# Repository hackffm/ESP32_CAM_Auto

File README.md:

# ESP32_CAM_Auto
ESP32 Camera FPV Car - some description also on our [Hackerspace-FFM e.V. FPV-Roboter page](https://www.hackerspace-ffm.de/wiki/index.php?title=FPV-Roboter)

# Software setup
## Initial programming of ESP32 CAM Module
Connect it to USB-Serial-Board, hit `Pioarduino -> Project Tasks -> esp32cam -> Custom -> Initial Erase + Flash + FS + Monitor`. 

## Architecture infos
- LittleFS is used to store and retrieve WiFi credentials, botname and motor configs. This usually survives a FW update if LittleFS is not uploaded as well. Defaults are used, but LittleFS must be initialized. 
- Camera streams over http port 81 in MJPG mode - this guarantees lowest latency as next frame is only tranferred if current frame was delivered. Usually no significant buffering is used in browsers (this is different for eg RTSP that is why it is not used)
- Code is optimized for OV3660 cameras and support OV2640 cameras. ESP32 CAM boards have known issues with extreme WiFi lag due EMI issues with camera clock signal. We are using the following trick: Reduce external camera clock from 20Mhz to 8Mhz, but then using camera interanl PLL to get same speed again, that way we face much less interference issues.
- http deliveres index.htm and info and action point on port 80. Info streams every second info to browser like fps, but also names for sliders. action is used for controlling everything that is send from browser to the ESP (steering but also settings).
- pwmThing class encapsulates all PWM actions to control LED brightness, set motor speed and servo positions.
- Care must be taken that PWM stuff like analogWrite usually used high-speed timers, but camera clock is using low-speed timers. Arduino does not know about the already used camera timers, but as it uses high-speed timers instead there is no conflict.

# Hardware setup
## Cabling with special PCB
With the special PCB cabling is as easy as connecting left and right motor to the upper 2pin row of the headers and the servo to the lower 3pin row of the headers. For servo, the control line (typical the yellow cable) goes to where the pin is missing on the row above.
If servo does not work, you might need to turn the connector - as long as all 3 pins are connected nothing should broke even if the connector is in the wrong direction. For motor, check that the motors turn forward if you control the joystick forward, otherwise just turn the 2pin connector to change the motor direction of that motor that rotates in the wrong direction.

Supply power from Power Bank via USB-C cable to PCB to turn on the robot. Beware that the PCB does not include the programming hardware for the ESP-CAM - you have to program the ESP-CAM module with a separate programming adapter and then transfer it to the motor driver PCB.

PCB preparation: The idea is that you cut Pin 1 (the one with the square pad on the PCB) away to get a 3+2 pol connector from that originally 2x3 pol connector.
## Manual cabling
- For full-bridge motor drivers connect inputs to 12+13 and 15+14, add connectors to the motors that you can easily swap or turn the motor lines to adjust for correct drive direction
- For 360° servos just pick two of the available pins and set them up via web interface for left and right motor
- We used an USB A plug and a power supply for suppy. In such a case wire separate cables for motors and for ESP32 beginning from USB plug to avoid issues that motor starting currents are affecting ESP32

See the following picture how we did it:

## Usable pins
Pins can be redefined via Webinterface but on ESP32 CAM only the following pins are selectable and usable: 
- -1 (if pin or function not needed)
- 2, 12, 13, 14, 15 (free for use, SD card can not be used as these are also for SD card)
- 3 (if used, serial RX is not available anymore)

The following pins can not be used even if they are available on the ESP32 CAM board:
- 0 is used for camera clock signal
- 16 is internally used for PSRAM
- 1 is used for serial TX
- 4 is controlling the white flash LED
- 33 is controlling the red internal LED (might be usable if RedLed PWMThing is connected to pin -1)

## Supported motors
Both servos and full-bridge motor drivers are supported. Currently only seperate left- and right-motor are supported (no steering servo). Servos can then be 360deg servos used as motors, adjust min/zero/max limits for servos, zero is where 360deg servos does not turn (but they are stopped if appropriate servo variant is selected anyway).

# Usage
## LED indications
Slow breathing red LED means normal operation and having a valid WiFi connection. You should be able to control your robot via website of the IP or the name the robot (default: http://cambot.local)

Fast breathing red LED means robot has not found a valid WiFi connection and is acting as WiFi access point. Scan you WiFi environment, connect to the WiFi that matches your robot name (default: cambot), and then go to http://192.168.4.1 to either control your robot directly or connect it to your home WiFi using the Settings area, where you could also scan for your WiFi access points. Beware that the ESP-CAM is 2.4GHz only, so you can connect it only access points that support 2.4GHz WiFi.

No breathing or blinking or off: Something is broken or not powered. If white LED blinks two times the modul could not start the camera module - so check the connection to the camera module first. Beware that to open the camera connector you have to twist the black element by 90° (meaning pulling it away from PCB surface) and not pull it along the PCB. Currently supported camera modules: OV2640 or OV3660 (recommended).

# Known issues
## It does not compile
Uninstall ESP32 core modules in Platform-IO first to force installing newest ones.

### This versions gave a running config
PACKAGES: 
 - contrib-piohome @ 3.4.4 
 - framework-arduinoespressif32 @ 3.3.7 
 - framework-arduinoespressif32-libs @ 5.5.0+sha.87912cd291 
 - tool-esp-rom-elfs @ 2024.10.11 
 - tool-esptoolpy @ 5.1.2 
 - toolchain-xtensa-esp-elf @ 14.2.0+20251107

## Connection issues
- Check Serial output for IP address and if Wifi connection worked.
- Most browsers need at least a slash at the end to not trigger the search engine, try `cambot/`first.
- Name server often have issues, mDNS is also active, try `cambot.local/`if IP can not be resolved.
- Some browsers tries always https, but only http is supported now, try `http://cambot.local`in such case.
- Last resort enter ip address in browser
- If WiFi credentials are not set, either set them via Serial terminal or connect to access point of the device, then open `http://192.168.4.1/`and set there Wifi SSID + password, then power cycle.

## FPS 
Ok, you want the picture as smooth as possible, why limit FPS then? If WiFi is too much congested, everything starts getting sluggy, especially if more than one FPV car is operated it can make sense to limit the frame rate to leave some room for other players. WiFi at 2.4 GHz can transmit around 3,000 kBytes/s (but an ESP32 max out usually already at 1,000 kBytes/s due internal limits), depending on quality settings and picture size we integrated at least 4 fpv cars in the band without issues simultaneously. Keep an eye on RSSI, if it falls below -70 dBm the WiFi bandwith starts to be limited significantly affecting also the frame rate of that vehicle.  

## Camera overheating
Especially the OV3660 moduls are working on ESP32 CAM boards, but are operated out of voltage specifications there. Therefore they are more prone to heat up - glue them with thin double sided tape to the SD card holder to give them a little more cooling surface. Camera is specified to operate with best picture quality up to 50°C, they are specified to allow operation up to 70°C, we see it often a little bit higher than that but it seems to be ok. As said, issue is that OV2640 is usually prefered over OV3660 du to better picture and speed but are more prone to overheating.

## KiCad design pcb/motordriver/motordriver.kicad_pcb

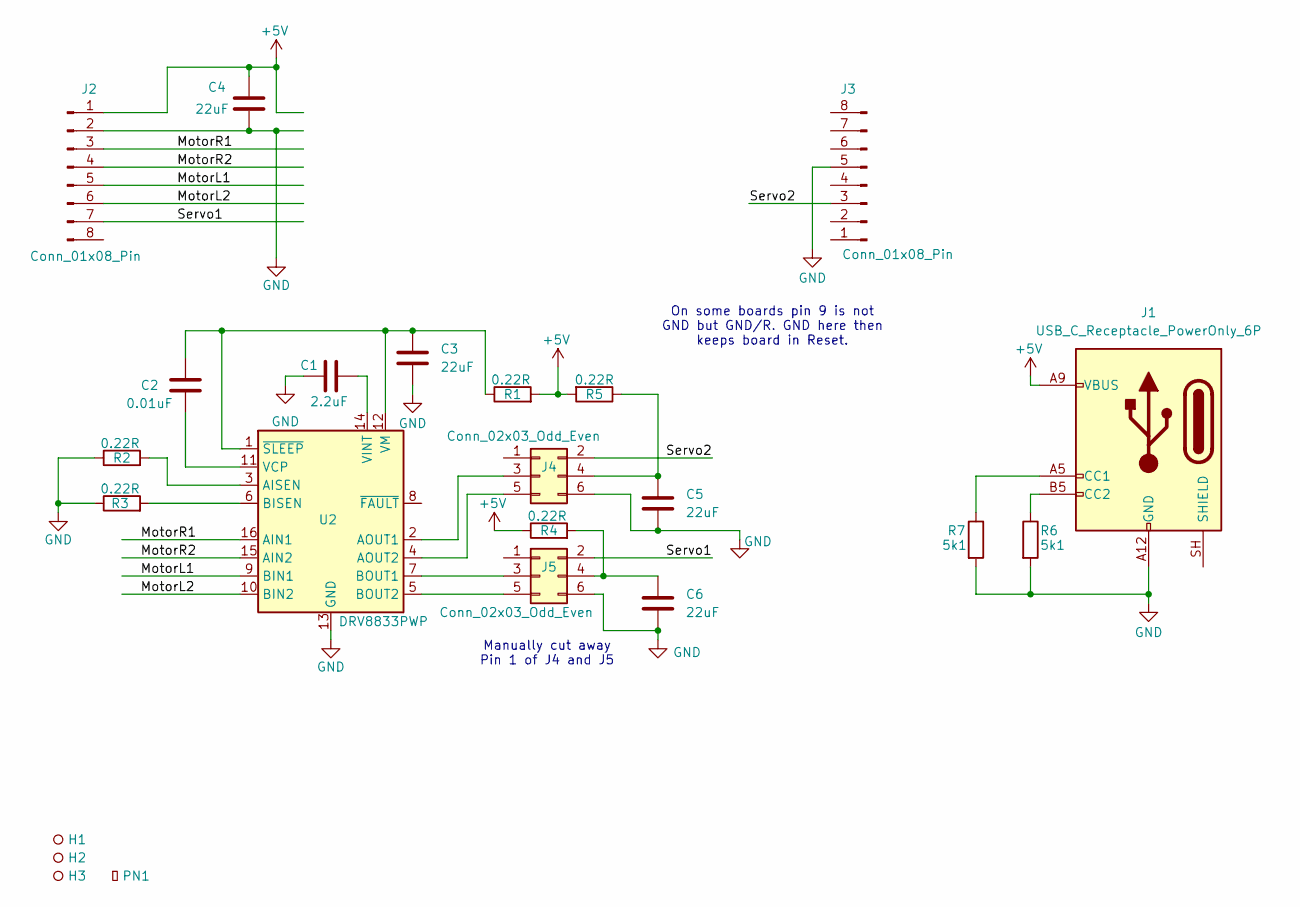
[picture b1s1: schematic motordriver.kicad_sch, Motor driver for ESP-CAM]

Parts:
C1: 2.2uF; C_0805_2012Metric; LCSC C377773
C2: 0.01uF; C_0603_1608Metric; LCSC C57112
C3, C4, C5, C6: 22uF; C_1206_3216Metric; LCSC C12891
H1, H2, H3: Hole_Tooling_JLCPCB
J1: USB_C_Receptacle_PowerOnly_6P; USB_C_Receptacle_HRO_TYPE-C-31-M-17; LCSC C283540
J2, J3: Conn_01x08_Pin; PinSocket_1x08_P2.54mm_Vertical; LCSC C22438158
J4, J5: Conn_02x03_Odd_Even; PinHeader_2x03_P2.54mm_Horizontal; LCSC C492431
PN1: Part_Num_JLCPCB
R1, R2, R3, R4, R5: 0.22R; R_1206_3216Metric; LCSC C327006
R6, R7: 5k1; R_0603_1608Metric; LCSC C23186
U2: DRV8833PWP; HTSSOP-16-1EP_4.4x5mm_P0.65mm_EP3.4x5mm_Mask2.46x2.31mm_The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; LCSC C50506

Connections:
+5V: C4.2, J1.A9 (VBUS), J1.B9 (VBUS), J2.1, R1.2, R4.1, R5.2
/MotorL1: J2.5, U2.9 (BIN1)
/MotorL2: J2.6, U2.10 (BIN2)
/MotorR1: J2.3, U2.16 (AIN1)
/MotorR2: J2.4, U2.15 (AIN2)
/Servo1: J2.7, J5.2
/Servo2: J3.3, J4.2
GND: C1.1, C3.2, C4.1, C5.2, C6.2, J1.A12 (GND), J1.B12 (GND), J2.2, J3.5, J4.6, J5.6, R2.1, R3.1, R6.2, R7.2, U2.13 (GND), U2.17 (GND)
unnamed: J1.A5 (CC1), R7.1
unnamed: J1.B5 (CC2), R6.1
unnamed: J4.3, U2.2 (AOUT1)
unnamed: C5.1, J4.4, R5.1
unnamed: J4.5, U2.4 (AOUT2)
unnamed: J5.3, U2.7 (BOUT1)
unnamed: C6.1, J5.4, R4.2
unnamed: J5.5, U2.5 (BOUT2)
unnamed: R2.2, U2.3 (AISEN)
unnamed: R3.2, U2.6 (BISEN)
unnamed: C2.2, U2.11 (VCP)
unnamed: C1.2, U2.14 (VINT)
unnamed: C2.1, C3.1, R1.1, U2.1 (~SLEEP), U2.12 (VM)

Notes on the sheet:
Manually cut away Pin 1 of J4 and J5
On some boards pin 9 is not GND but GND/R. GND here then keeps board in Reset.

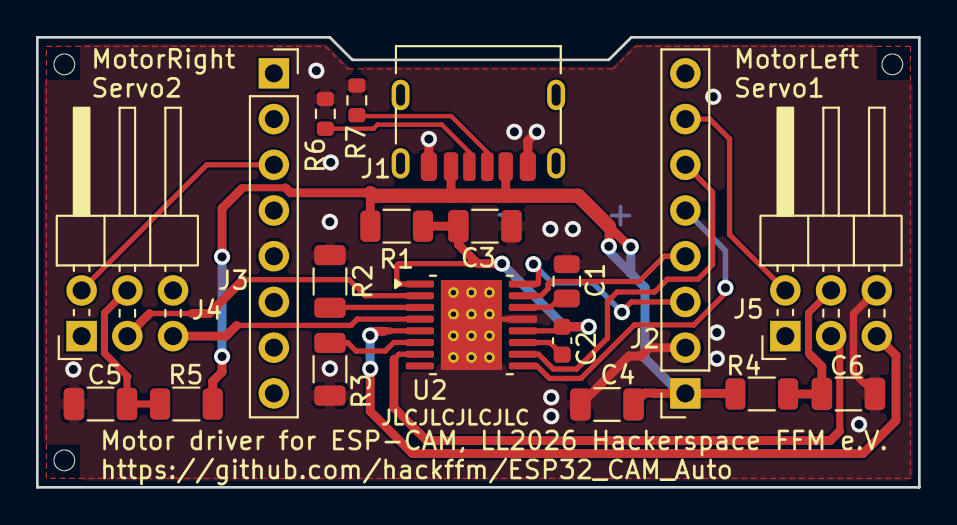
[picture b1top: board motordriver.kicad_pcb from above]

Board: 2 copper layers, 49.0 x 25.0 mm, 23 parts (0 on the bottom side), 21 nets.

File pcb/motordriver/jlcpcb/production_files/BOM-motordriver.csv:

Comment,Designator,Footprint,LCSC,Quantity
0.01uF,C2,C_0603_1608Metric,C57112,1
0.22R,"R1,R2,R3,R4,R5",R_1206_3216Metric,C327006,5
2.2uF,C1,C_0805_2012Metric,C377773,1
22uF,"C3,C4,C5,C6",C_1206_3216Metric,C12891,4
5k1,"R6,R7",R_0603_1608Metric,C23186,2
Conn_01x08_Pin,"J2,J3",PinSocket_1x08_P2.54mm_Vertical,C22438158,2
Conn_02x03_Odd_Even,"J4,J5",PinHeader_2x03_P2.54mm_Horizontal,C492431,2
DRV8833PWP,U2,HTSSOP-16-1EP_4.4x5mm_P0.65mm_EP3.4x5mm_Mask2.46x2.31mm_ThermalVias,C50506,1
USB_C_Receptacle_PowerOnly_6P,J1,USB_C_Receptacle_HRO_TYPE-C-31-M-17,C283540,1
~,H3,Hole_Tooling_JLCPCB,,1
~,H2,Hole_Tooling_JLCPCB,,1
~,H1,Hole_Tooling_JLCPCB,,1
~,PN1,Part_Num_JLCPCB,,1

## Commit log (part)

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2026-02-23 More adjustments to Webseite, added servo control
2026-03-09 Optimized
2026-03-23 Fixed camera lag issues
2026-03-27 Moved index to Littlefs, added gamepad control
2026-03-27 Clean up, OTA working again, Wifi credentials via http
2026-03-28 fixes
2026-03-28 gamepad optimization
2026-03-28 servo update
2026-03-28 servo optimiert
2026-04-04 Optimizations
2026-04-13 Add PCB dev (not finished)
2026-05-24 PCB created
2026-05-26 Updated PCB, fixed minor bugs on PCB
2026-06-01 Settings to extra page and other changes
2026-06-01 Added ml mr command
2026-06-07 Under the hood adjustments, on-screen buttons still missing...
2026-06-08 Buttons working
2026-06-08 last
2026-06-11 Quite good
2026-06-12 Finetune
